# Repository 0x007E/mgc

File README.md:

# `MGC` - MeGARCard

The `MGC` is built as base development board with a set of push-buttons, leds, potentiometers and many more components on-board. It builds the base platform for a bunchset of adaptable microcontrolles (e.g. `ATmega16A`, `ATmega4808`, `ESP32`). It simplifies the development process by extending supported microcontrollers to a range of actuators and sensors. The board itself regulates the voltage to `5V` or `3V3` automatically with a power mux ([TPS2116](#additional-information)). If `3V3` and `5V` are suppored, the voltage can be changed on the dip switch of the adaptable microcontroller board. The base board supports a usb or uart-interface [FT230XS](#additional-information) to the adaptable microcontroller. The usb mode can be switched over a usb-multiplexer [TS3USB30](#additional-information) within the dip switch on the base board. The leds on the base bord are controlled over a transistor array [TBD62783](#additional-information) that keeps the input current on a very low state. 

> Note that the board should be disconnected from power sources when changing the state of the dip switches on the base or microcontroller adapter board.

| Experience  | Level                                                                               |
|:------------|:-----------------------------------------------------------------------------------:|
| Soldering   |  |
| Mechanical  |     |

# Adapter-Boards

| ATmega16A | ATmega4809 | ESP32 |
|:---------:|:----------:|:-----:|
|  |  |  |
| Schematic | Schematic | Schematic |
| [pdf](https://github.com/0x007E/mgc_m16a/releases/latest/download/schematic.pdf) / [cadlab](https://cadlab.io/project/30414/main/files) | [pdf](https://github.com/0x007E/mgc_m4809/releases/latest/download/schematic.pdf) / [cadlab](https://cadlab.io/project/30419/main/files) | [pdf](https://github.com/0x007E/mgc_esp32/releases/latest/download/schematic.pdf) / [cadlab](https://cadlab.io/project/30425/main/files) |
| [GitHub](https://github.com/0x007e/mgc_m16a) | [GitHub](https://github.com/0x007e/mgc_m4809) | [GitHub](https://github.com/0x007e/mgc_esp32) |

# Downloads

| Type      | File                                                                                                                                                 | Description     |
|:---------:|:----------------------------------------------------------------------------------------------------------------------------------------------------:|:----------------|
| Schematic | [pdf](https://github.com/0x007E/mgc/releases/latest/download/schematic.pdf) / [cadlab](https://cadlab.io/project/30413/main/files)                   | Schematic files |
| Board     | [pdf](https://github.com/0x007E/mgc/releases/latest/download/pcb.pdf) / [cadlab](https://cadlab.io/project/30413/main/files)                         | Board file      |
| Drill     | [pdf](https://github.com/0x007E/mgc/releases/latest/download/drill.pdf)                                                                              | Drill file      |
| BoM | [xlsx](https://github.com/0x007E/mgc/releases/latest/download/bom.xlsx) / [html](https://github.com/0x007E/mgc/releases/latest/download/ibom.html)          | Bill of Material as Excel/interactive HTML |
| PCB    | [zip](https://github.com/0x007E/mgc/releases/latest/download/kicad.zip) / [tar](https://github.com/0x007E/mgc/releases/latest/download/kicad.tar.gz)    | KiCAD/Gerber/BoM/Drill files       |
| Mechanical | [zip](https://github.com/0x007E/mgc/releases/latest/download/freecad.zip) / [tar](https://github.com/0x007E/mgc/releases/latest/download/freecad.tar.gz) | FreeCAD/Housing and PCB (STEP/STL) files     |

# Hardware

The pcb is created with `KiCAD`, the housing with `FreeCAD`. All files are built with `github actions` so that they are ready for a production environment.

## PCB

The circuit board is populated on both sides (Top, Bottom). The best way for soldering the `SMD` components is within a vapor phase soldering system and for the `THT` components with a standard soldering system.

### Top Layer

### Bottom Layer

## Mechanical

The housing has a tolerance of `0.2mm` on each side of the case. So the pcb should fit perfectly in the housing. The tolerance can be modified with `FreeCAD` in the `Parameter` Spreadsheet.

### Assembled

### Exploded

# Additional Information

| Type       | Link               | Description              |
|:----------:|:------------------:|:-------------------------|
| FT230XS    | [pdf](https://ftdichip.com/wp-content/uploads/2021/10/DS_FT230X.pdf) | USB/UART-Bridge |
| TS3USB30 | [pdf](https://www.ti.com/lit/ds/symlink/ts3usb30e.pdf) | USB-Multiplexer 1:2 |
| TPS2116 | [pdf](https://www.ti.com/lit/ds/symlink/tps2116.pdf) | Power Mux with Manual and Priority Switchover |
| TBD62783 | [pdf](https://toshiba.semicon-storage.com/info/datasheet_en_20160511.pdf) | DMOS transistor array |

---

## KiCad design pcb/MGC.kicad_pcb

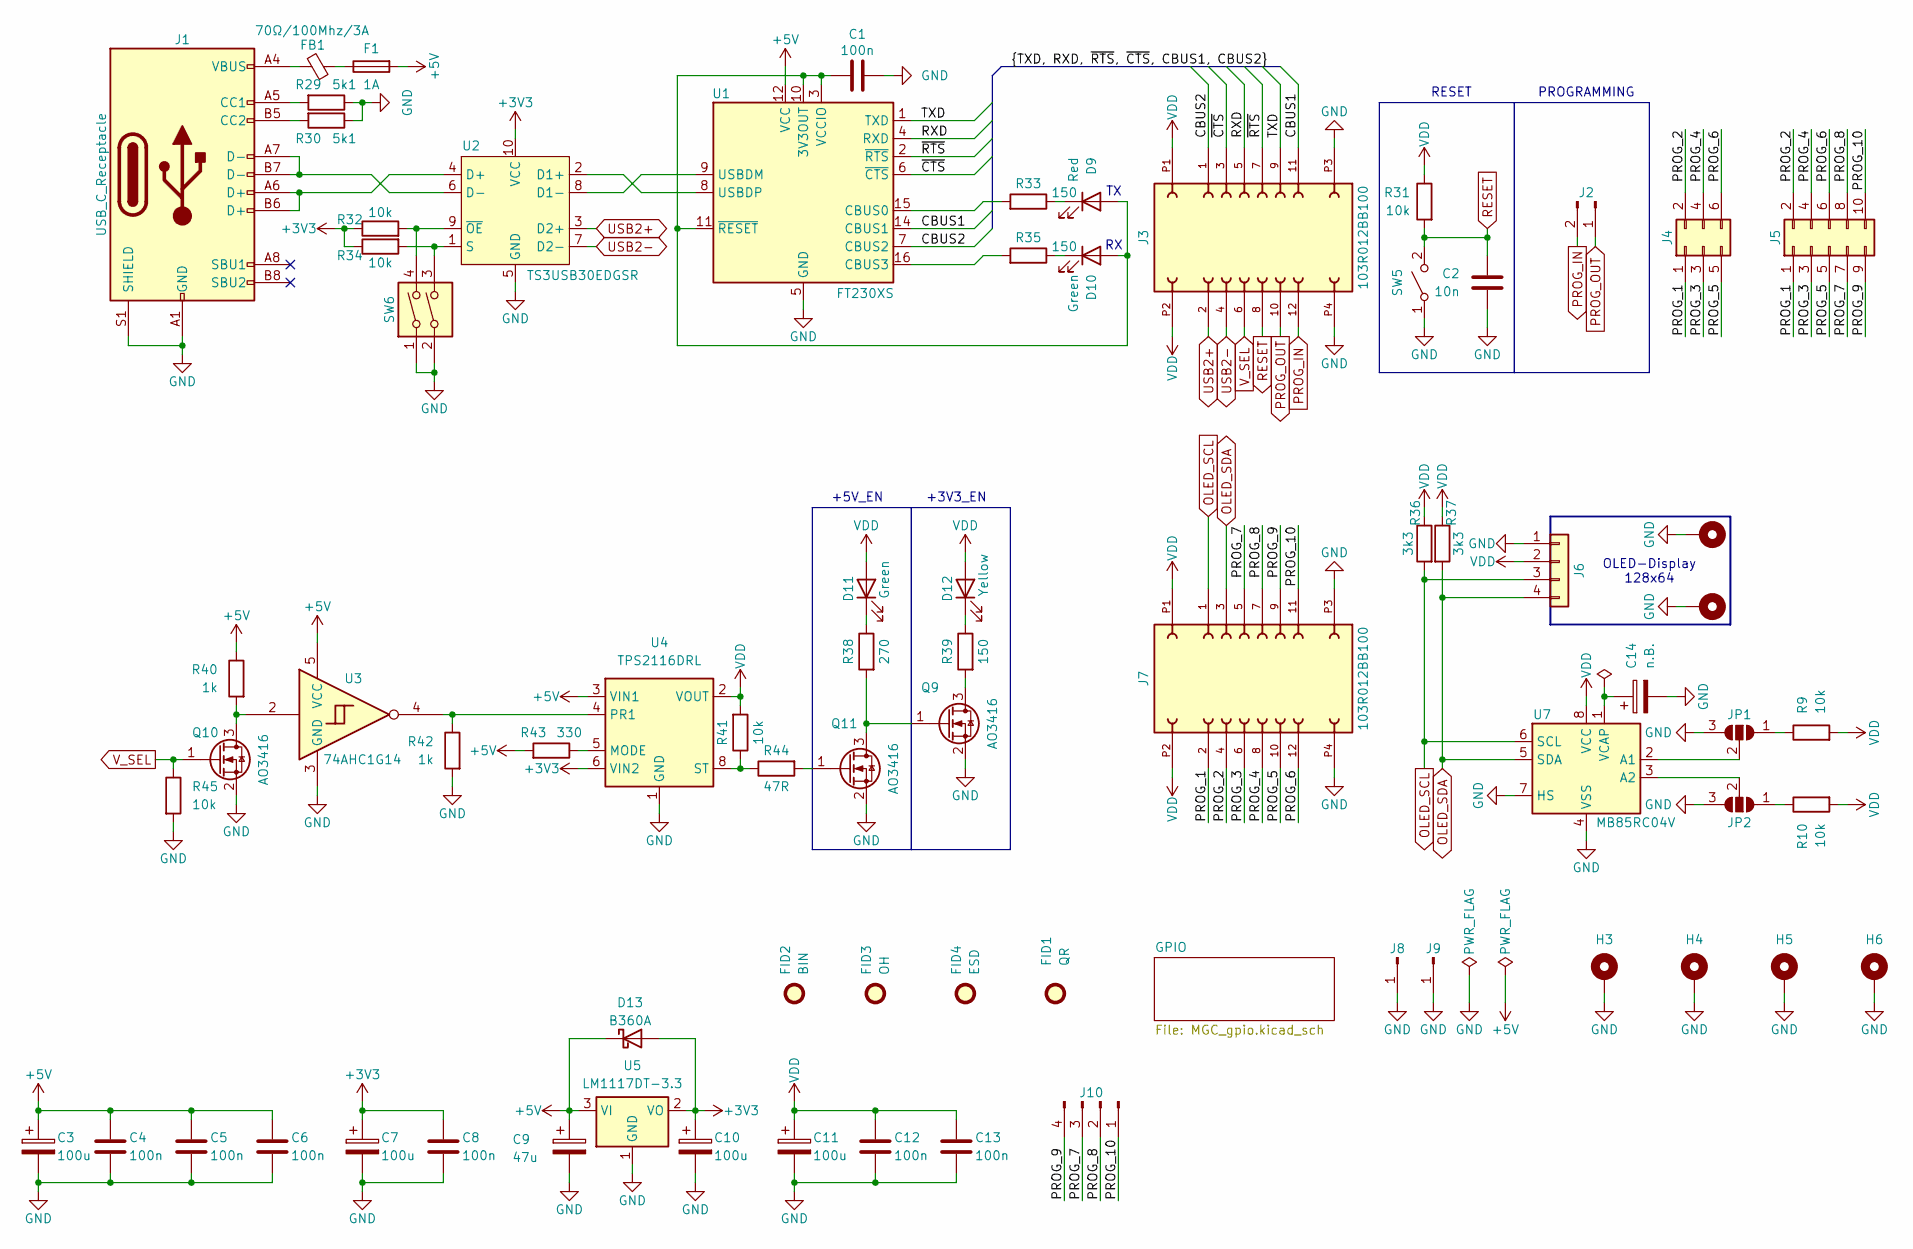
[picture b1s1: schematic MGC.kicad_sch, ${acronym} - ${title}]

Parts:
C1, C4, C5, C6, C8, C12, C13: 100n; C_1206_3216Metric
C2: 10n; C_0603_1608Metric
C3, C7, C10, C11: 100u; CP_EIA-3528-21_Kemet-B; DigiKey 478-3877-1-ND
C9: 47u; CP_EIA-6032-28_Kemet-C
C14: n.B.; CP_EIA-3528-21_Kemet-B
D9: Red; LED_1206_3216Metric
D10, D11: Green; LED_1206_3216Metric
D12: Yellow; LED_1206_3216Metric
D13: B360A; D_SMA
F1: 1A; Fuse_1206_3216Metric; DigiKey 5923-0ZCJ0100FF2ECT-ND
FB1: 70Ω/100Mhz/3A; L_1206_3216Metric
FID1: QR; QR_0x007e_very_small
FID2: BIN; WEEE-Logo_4.2x6mm_SilkScreen
FID3: OH; OSHW-Logo2_7.3x6mm_SilkScreen
FID4: ESD; ESD-Logo_6.6x6mm_SilkScreen
H1, H2, H3, H4, H5, H6: MountingHole_Pad; MountingHole_2.7mm_M2.5_DIN965_Pad
J1: USB_C_Receptacle; USB_C_Receptacle_GCT_USB4110
J2: Conn_01x02_Pin; PinHeader_1x02_P2.54mm_Vertical_SMD_Pin1Right; DigiKey HDR100IMP40M-G-V-SM-ND
J3, J7: 103R012BB100; AMPHENOL_103R012BB100; DigiKey 609-103R012BB100CT-ND
J4: Conn_02x03_Odd_Even; AMPHENOL_20021221-00006T4LF; DigiKey 609-20021221-00006T4LF-ND
J5: Conn_02x05_Odd_Even; AMPHENOL_20021521-00010T4LF; DigiKey 1175-1629-ND
J6: Conn_01x04; PinSocket_1x04_P2.54mm_Vertical
J8, J9: Conn_01x01_Pin; SolderWire-0.75sqmm_1x01_D1.25mm_OD3.5mm
J10: Conn_01x04_Pin; PinSocket_1x04_P2.54mm_Vertical_SMD_Pin1Right; DigiKey S5596-ND
JP1, JP2: SolderJumper_3_Open; SolderJumper-3_P1.3mm_Open_RoundedPad1.0x1.5mm_NumberLabels
Q9, Q10, Q11: AO3416; SOT-23
R9, R10, R31, R32, R34, R41, R45: 10k; R_1206_3216Metric
R29, R30: 5k1; R_1206_3216Metric
R33, R35, R39: 150; R_1206_3216Metric
R36, R37: 3k3; R_1206_3216Metric
R38: 270; R_1206_3216Metric
R40, R42: 1k; R_1206_3216Metric
R43: 330; R_1206_3216Metric
R44: 47R; R_1206_3216Metric
SW5: SW_SPST; SW_SPST_B3S-1000
SW6: SW_DIP_x02; SW_DIP_SPSTx02_Slide_6.7x6.64mm_W6.73mm_P2.54mm_LowProfile_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
U1: FT230XS; SSOP-16_3.9x4.9mm_P0.635mm
U2: TS3USB30EDGSR; VSSOP-10_3x3mm_P0.5mm; DigiKey 296-25495-1-ND
U3: 74AHC1G14; SOT-23-5
U4: TPS2116DRL; SOT-583-8; DigiKey 296-TPS2116DRLRCT-ND
U5: LM1117DT-3.3; TO-252-3_TabPin2
U7: MB85RC04V; SOIC-8_3.9x4.9mm_P1.27mm; DigiKey 47C16-I/SN-ND, 865-MB85RC04VPNF-G-AMERE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

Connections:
+3V3: C7.1, C8.1, C10.1, D13.2 (A), R32.1, R34.1, U2.10 (VCC), U4.6 (VIN2), U5.2 (VO)
+5V: C3.1, C4.1, C5.1, C6.1, C9.1, D13.1 (K), F1.2, R40.1, R43.2, U1.12 (VCC), U3.5 (VCC), U4.3 (VIN1), U5.3 (VI); also elsewhere on the board
/CBUS1: J3.11, U1.14 (CBUS1)
/CBUS2: J3.1, U1.7 (CBUS2)
/PROG_1: J4.1, J5.1, J7.2
/PROG_2: J4.2, J5.2, J7.4
/PROG_3: J4.3, J5.3, J7.6
/PROG_4: J4.4, J5.4, J7.8
/PROG_5: J4.5, J5.5, J7.10
/PROG_6: J4.6, J5.6, J7.12
/PROG_7: J5.7, J7.5, J10.3
/PROG_8: J5.8, J7.7, J10.2
/PROG_9: J5.9, J7.9, J10.4
/PROG_10: J5.10, J7.11, J10.1
/RXD: J3.5, U1.4 (RXD)
/TXD: J3.9, U1.1 (TXD)
/~CTS: J3.3, U1.6 (~CTS)
/~RTS: J3.7, U1.2 (~RTS)
GND: C1.2, C2.2, C3.2, C4.2, C5.2, C6.2, C7.2, C8.2, C9.2, C10.2, C11.2, C12.2, C13.2, C14.2, H1.1, H2.1, H3.1, H4.1, H5.1, H6.1, J1.A1 (GND), J1.A12 (GND), J1.B1 (GND), J1.B12 (GND), J1.S1 (SHIELD), J3.P3, J3.P4, J6.1, J7.P3, J7.P4, J8.1, J9.1, JP1.3 (B), JP2.3 (B), Q9.2 (S), Q10.2 (S), Q11.2 (S), R29.1, R30.1, R42.2, R45.2, SW5.1 (A), SW6.1, SW6.2, U1.5 (GND), U1.13 (GND), U2.5 (GND), U3.3 (GND), U4.1 (GND), U5.1 (GND), U7.4 (VSS), U7.7 (HS); also elsewhere on the board
unnamed: D9.1 (K), R33.1
unnamed: C1.1, D9.2 (A), D10.2 (A), U1.3 (VCCIO), U1.10 (3V3OUT), U1.11 (~RESET)
unnamed: D10.1 (K), R35.1
unnamed: D11.1 (K), R38.1
unnamed: D12.1 (K), R39.1
unnamed: F1.1, FB1.1
unnamed: FB1.2, J1.A4 (VBUS), J1.A9 (VBUS), J1.B4 (VBUS), J1.B9 (VBUS)
unnamed: J1.A5 (CC1), R29.2
unnamed: J1.B5 (CC2), R30.2
unnamed: JP1.1 (A), R9.1
unnamed: JP1.2 (C), U7.2 (A1)
unnamed: JP2.1 (A), R10.1
unnamed: JP2.2 (C), U7.3 (A2)
unnamed: Q9.3 (D), R39.2
unnamed: Q10.3 (D), R40.2, U3.2
unnamed: Q9.1 (G), Q11.3 (D), R38.2
unnamed: Q11.1 (G), R44.2
unnamed: R33.2, U1.15 (CBUS0)
unnamed: R35.2, U1.16 (CBUS3)
unnamed: U1.9 (USBDM), U2.8 (D1-)
unnamed: U1.8 (USBDP), U2.2 (D1+)
unnamed: J1.A6 (D+), J1.B6 (D+), U2.4 (D+)
unnamed: J1.A7 (D-), J1.B7 (D-), U2.6 (D-)
unnamed: R34.2, SW6.3, U2.1 (S)
unnamed: R32.2, SW6.4, U2.9 (~OE)
unnamed: R43.1, U4.5 (MODE)
unnamed: R42.1, U3.4, U4.4 (PR1)
unnamed: R41.1, R44.1, U4.8 (ST)
unnamed: C14.1, U7.1 (VCAP)
OLED_SCL: J6.3, J7.1, R36.2, U7.6 (SCL)
OLED_SDA: J6.4, J7.3, R37.2, U7.5 (SDA)
PROG_IN: J2.2, J3.12
PROG_OUT: J2.1, J3.10
RESET: C2.1, J3.8, R31.2, SW5.2 (B)
USB2+: J3.2, U2.3 (D2+)
USB2-: J3.4, U2.7 (D2-)
VDD: C11.1, C12.1, C13.1, D11.2 (A), D12.2 (A), J3.P1, J3.P2, J6.2, J7.P1, J7.P2, R9.2, R10.2, R31.1, R36.1, R37.1, R41.2, U4.2 (VOUT), U4.7 (VOUT), U7.8 (VCC); also elsewhere on the board
V_SEL: J3.6, Q10.1 (G), R45.1

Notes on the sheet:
PROGRAMMING
+3V3_EN
OLED-Display 128x64
RESET
+5V_EN

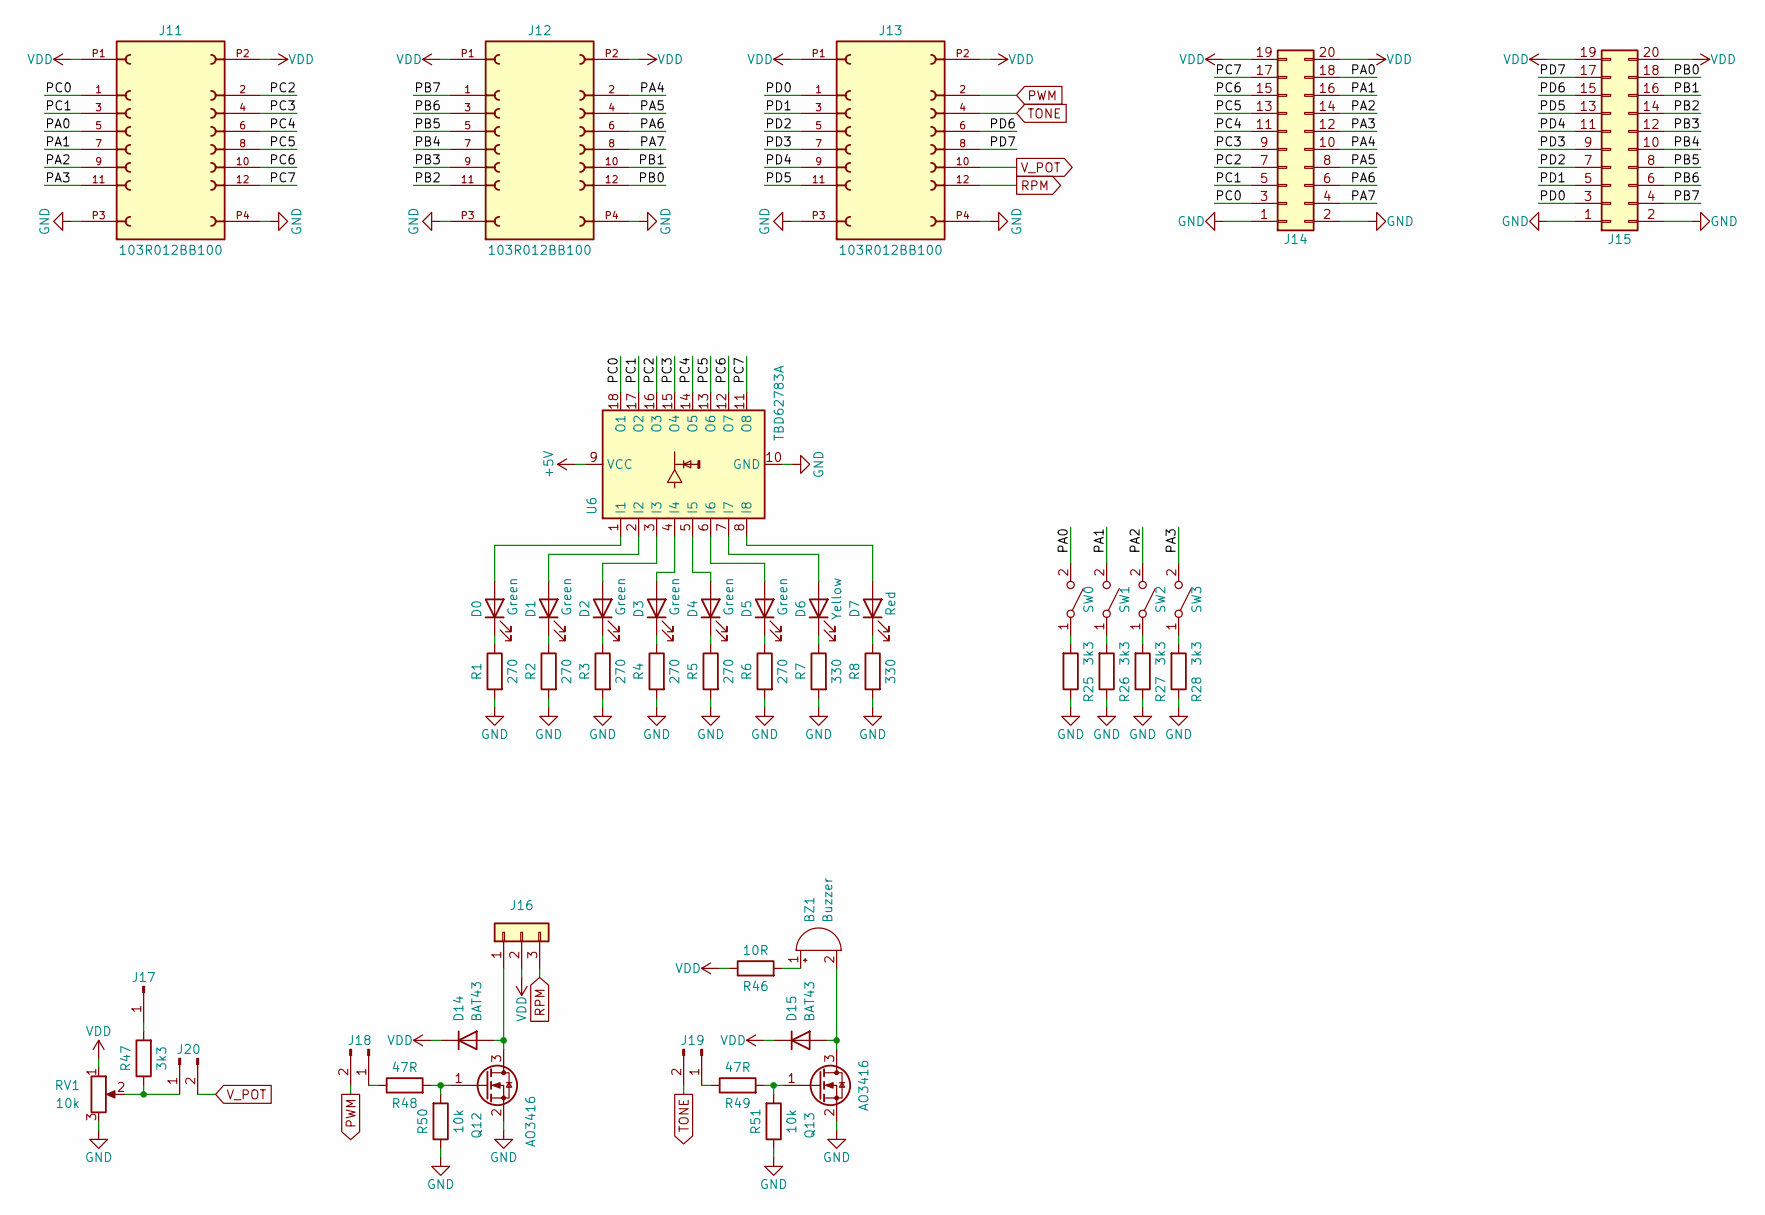
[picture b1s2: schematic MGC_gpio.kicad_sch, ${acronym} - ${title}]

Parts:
BZ1: Buzzer; MagneticBuzzer_ProSignal_ABT-410-RC
D0, D1, D2, D3, D4, D5: Green; LED_1206_3216Metric
D6: Yellow; LED_1206_3216Metric
D7: Red; LED_1206_3216Metric
D14, D15: BAT43; D_MiniMELF
J11, J12, J13: 103R012BB100; AMPHENOL_103R012BB100; DigiKey 609-103R012BB100CT-ND
J14, J15: Conn_02x10_Odd_Even; PinSocket_2x10_P2.54mm_Horizontal
J16: Conn_01x03; Molex_KK-254_AE-6410-03A_1x03_P2.54mm_Vertical; DigiKey WM4201-ND
J17: Conn_01x01_Pin; PinHeader_1x01_P2.54mm_Vertical
J18, J19, J20: Conn_01x02_Pin; PinHeader_1x02_P2.54mm_Vertical_SMD_Pin1Right; DigiKey HDR100IMP40M-G-V-SM-ND
Q12, Q13: AO3416; SOT-23
R1, R2, R3, R4, R5, R6: 270; R_1206_3216Metric
R7, R8: 330; R_1206_3216Metric
R25, R26, R27, R28, R47: 3k3; R_1206_3216Metric
R46: 10R; R_1206_3216Metric
R48, R49: 47R; R_1206_3216Metric
R50, R51: 10k; R_1206_3216Metric
RV1: 10k; Potentiometer_Piher_PT-10-V10_Vertical
SW0, SW1, SW2, SW3: SW_SPST; SW_SPST_B3S-1000
U6: TBD62783A; SOIC-18W_7.5x11.6mm_P1.27mm; DigiKey TBD62783AFGELCT-ND

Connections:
+5V: U6.9 (VCC); also elsewhere on the board
/GPIO/PA0: J11.5, J14.18, SW0.2 (B)
/GPIO/PA1: J11.7, J14.16, SW1.2 (B)
/GPIO/PA2: J11.9, J14.14, SW2.2 (B)
/GPIO/PA3: J11.11, J14.12, SW3.2 (B)
/GPIO/PA4: J12.2, J14.10
/GPIO/PA5: J12.4, J14.8
/GPIO/PA6: J12.6, J14.6
/GPIO/PA7: J12.8, J14.4
/GPIO/PB0: J12.12, J15.18
/GPIO/PB1: J12.10, J15.16
/GPIO/PB2: J12.11, J15.14
/GPIO/PB3: J12.9, J15.12
/GPIO/PB4: J12.7, J15.10
/GPIO/PB5: J12.5, J15.8
/GPIO/PB6: J12.3, J15.6
/GPIO/PB7: J12.1, J15.4
/GPIO/PC0: J11.1, J14.3, U6.18 (O1)
/GPIO/PC1: J11.3, J14.5, U6.17 (O2)
/GPIO/PC2: J11.2, J14.7, U6.16 (O3)
/GPIO/PC3: J11.4, J14.9, U6.15 (O4)
/GPIO/PC4: J11.6, J14.11, U6.14 (O5)
/GPIO/PC5: J11.8, J14.13, U6.13 (O6)
/GPIO/PC6: J11.10, J14.15, U6.12 (O7)
/GPIO/PC7: J11.12, J14.17, U6.11 (O8)
/GPIO/PD0: J13.1, J15.3
/GPIO/PD1: J13.3, J15.5
/GPIO/PD2: J13.5, J15.7
/GPIO/PD3: J13.7, J15.9
/GPIO/PD4: J13.9, J15.11
/GPIO/PD5: J13.11, J15.13
/GPIO/PD6: J13.6, J15.15
/GPIO/PD7: J13.8, J15.17
GND: J11.P3, J11.P4, J12.P3, J12.P4, J13.P3, J13.P4, J14.1, J14.2, J15.1, J15.2, Q12.2 (S), Q13.2 (S), R1.2, R2.2, R3.2, R4.2, R5.2, R6.2, R7.2, R8.2, R25.1, R26.1, R27.1, R28.1, R50.1, R51.1, RV1.3, U6.10 (GND); also elsewhere on the board
unnamed: BZ1.1 (+), R46.2
unnamed: BZ1.2 (-), D15.2 (A), Q13.3 (D)
unnamed: D0.2 (A), U6.1 (I1)
unnamed: D0.1 (K), R1.1
unnamed: D1.2 (A), U6.2 (I2)
unnamed: D1.1 (K), R2.1
unnamed: D2.2 (A), U6.3 (I3)
unnamed: D2.1 (K), R3.1
unnamed: D3.2 (A), U6.4 (I4)
unnamed: D3.1 (K), R4.1
unnamed: D4.2 (A), U6.5 (I5)
unnamed: D4.1 (K), R5.1
unnamed: D5.2 (A), U6.6 (I6)
unnamed: D5.1 (K), R6.1
unnamed: D6.2 (A), U6.7 (I7)
unnamed: D6.1 (K), R7.1
unnamed: D7.2 (A), U6.8 (I8)
unnamed: D7.1 (K), R8.1
unnamed: D14.2 (A), J16.1, Q12.3 (D)
unnamed: J17.1, R47.2
unnamed: J18.1, R48.1
unnamed: J19.1, R49.1
unnamed: J20.1, R47.1, RV1.2
unnamed: Q12.1 (G), R48.2, R50.2
unnamed: Q13.1 (G), R49.2, R51.2
unnamed: R25.2, SW0.1 (A)
unnamed: R26.2, SW1.1 (A)
unnamed: R27.2, SW2.1 (A)
unnamed: R28.2, SW3.1 (A)
PWM: J13.2, J18.2
RPM: J13.12, J16.3
TONE: J13.4, J19.2
VDD: D14.1 (K), D15.1 (K), J11.P1, J11.P2, J12.P1, J12.P2, J13.P1, J13.P2, J14.19, J14.20, J15.19, J15.20, J16.2, R46.1, RV1.1; also elsewhere on the board
V_POT: J13.10, J20.2

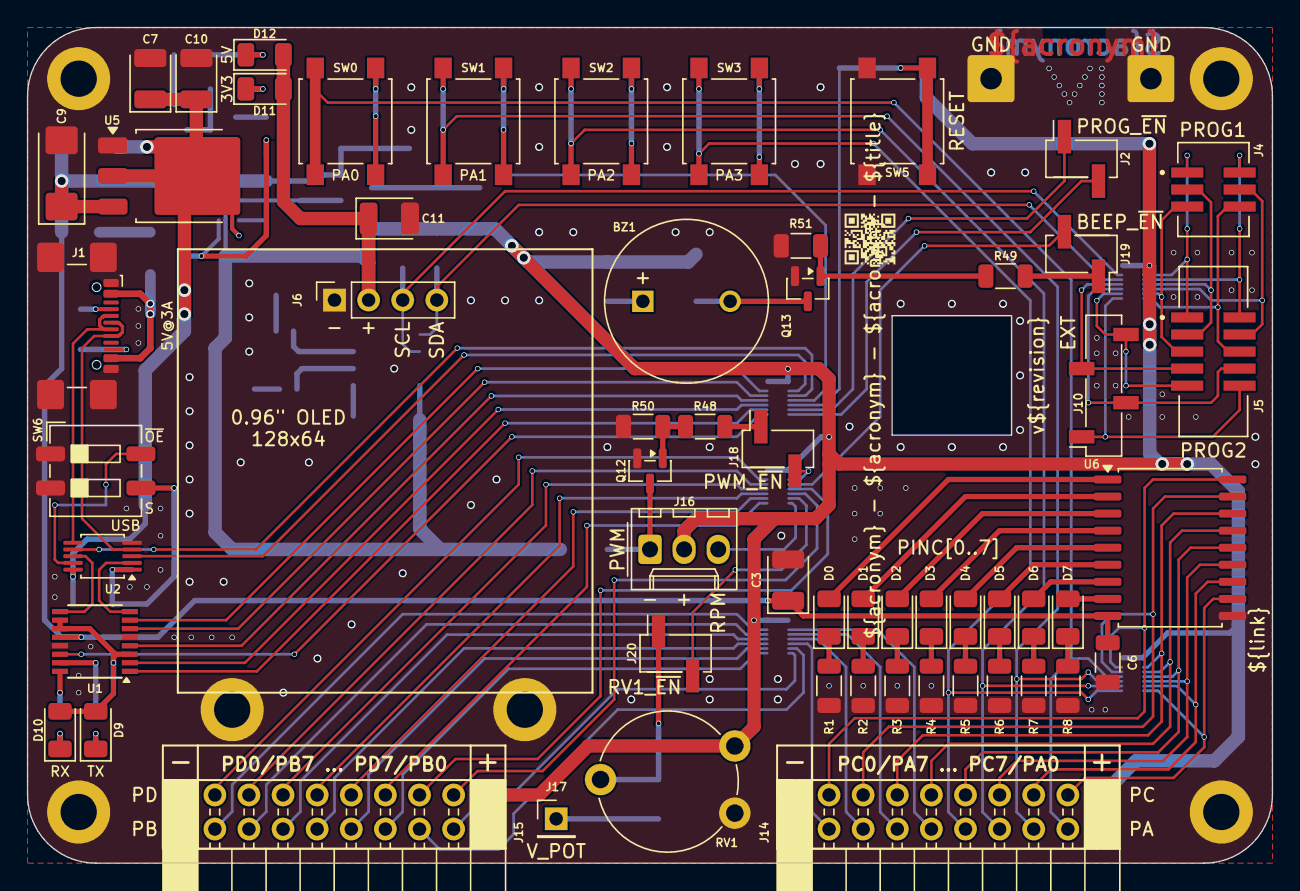
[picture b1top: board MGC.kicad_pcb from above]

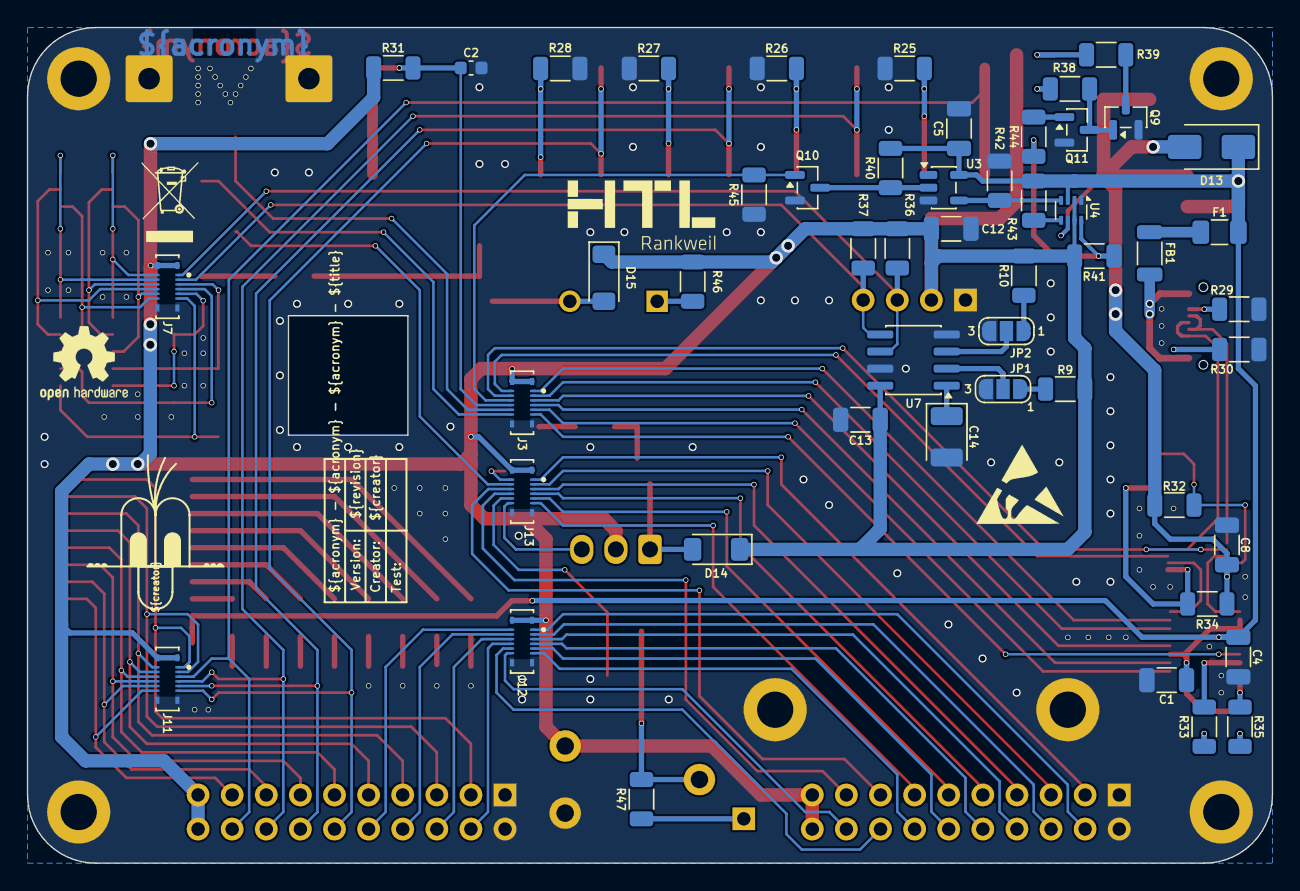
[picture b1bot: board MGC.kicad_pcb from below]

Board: 2 copper layers, 92.7 x 62.2 mm, 120 parts (54 on the bottom side), 122 nets.

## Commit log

2026-06-08 Add pcb layout
2026-06-09 Optimize fabrication layer
2026-06-09 Adapt device values
2026-06-09 Add missing vendor(id)
2026-06-09 Fix connector pin direction
2026-06-09 Add dimensioning
2026-06-09 Fix wrong acronym
2026-06-09 Fix wrong label direction
2026-06-11 Change reset capacitor device size
2026-06-13 Device repositioning
2026-06-13 Move display mounting hole
2026-06-15 Fix wrong connector dimension
2026-06-15 Add missing dimensions
2026-06-15 Add mechanical parts
2026-06-15 Adapt display position
2026-06-15 Add assembly explosion
2026-06-16 Add README.md
2026-06-16 Add build pipeline
2026-06-16 Add release pipeline
2026-06-17 Change adapter board images to thumbnails
2026-06-18 Fix wrong module links
2026-06-23 Adapt output filenames
2026-06-23 Add missing values in bom
2026-06-23 Adapt config and update action versions
2026-06-23 Add manufactor to bom
2026-06-23 Fix thumbnail image reference

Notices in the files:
README.md:
License CC By-NC-SA
parts and their libraries:
license: CC BY-NC-SA 4.0
